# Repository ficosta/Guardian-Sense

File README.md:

# GuardianSense

**GuardianSense** is a versatile hardware project based on the ESP32-S3, designed to monitor environmental conditions and provide real-time data to **Zabbix**. This board is compact yet powerful, integrating multiple sensors for a wide range of applications, including data centers, smart homes, and industrial environments.

## Features

- **Core Module**: ESP32-S3-WROOM-1 for Wi-Fi and BLE connectivity.
- **Environmental Sensors**:
  - Temperature and Humidity (BME280)
  - Smoke Detection (MQ-2)
  - Light Intensity (BH1750)
  - Presence Detection (AM312 PIR Sensor)
  - Vibration Monitoring (LDT0-028K)
  - Noise Level Monitoring (MAX9814)
- **Indicators**:
  - Status LED (Single color)
  - RGB LED (SK6812-MINI-E)
- **Connectivity**:
  - USB-C for power and data
  - Multiple GPIOs for additional customizations
- **Power Management**:
  - Integrated voltage regulator for 3.3V operation.

## Firmware

The firmware for GuardianSense is tailored to interact with **Zabbix**, providing seamless integration with this monitoring platform. It supports real-time data transmission for:

- Temperature and humidity
- Smoke and gas levels
- Light intensity
- Vibration and noise detection

## Usage

1. Clone this repository:
   ```bash
   git clone https://github.com/ficosta/Guardian-Sense.git
   ```

2. Install KiCad for hardware design modifications (optional).

3. Flash the firmware to the ESP32-S3 module.

4. Configure Zabbix to accept incoming data from the board.

## KiCad Design Files

All hardware design files for GuardianSense are included in the `/hardware` directory. Make sure to follow the project's **.gitignore** for KiCad files when contributing.

## Contributing

Contributions are welcome! Please ensure that any hardware or firmware changes align with the project's goals.

## License

See the `LICENSE` file for more details.

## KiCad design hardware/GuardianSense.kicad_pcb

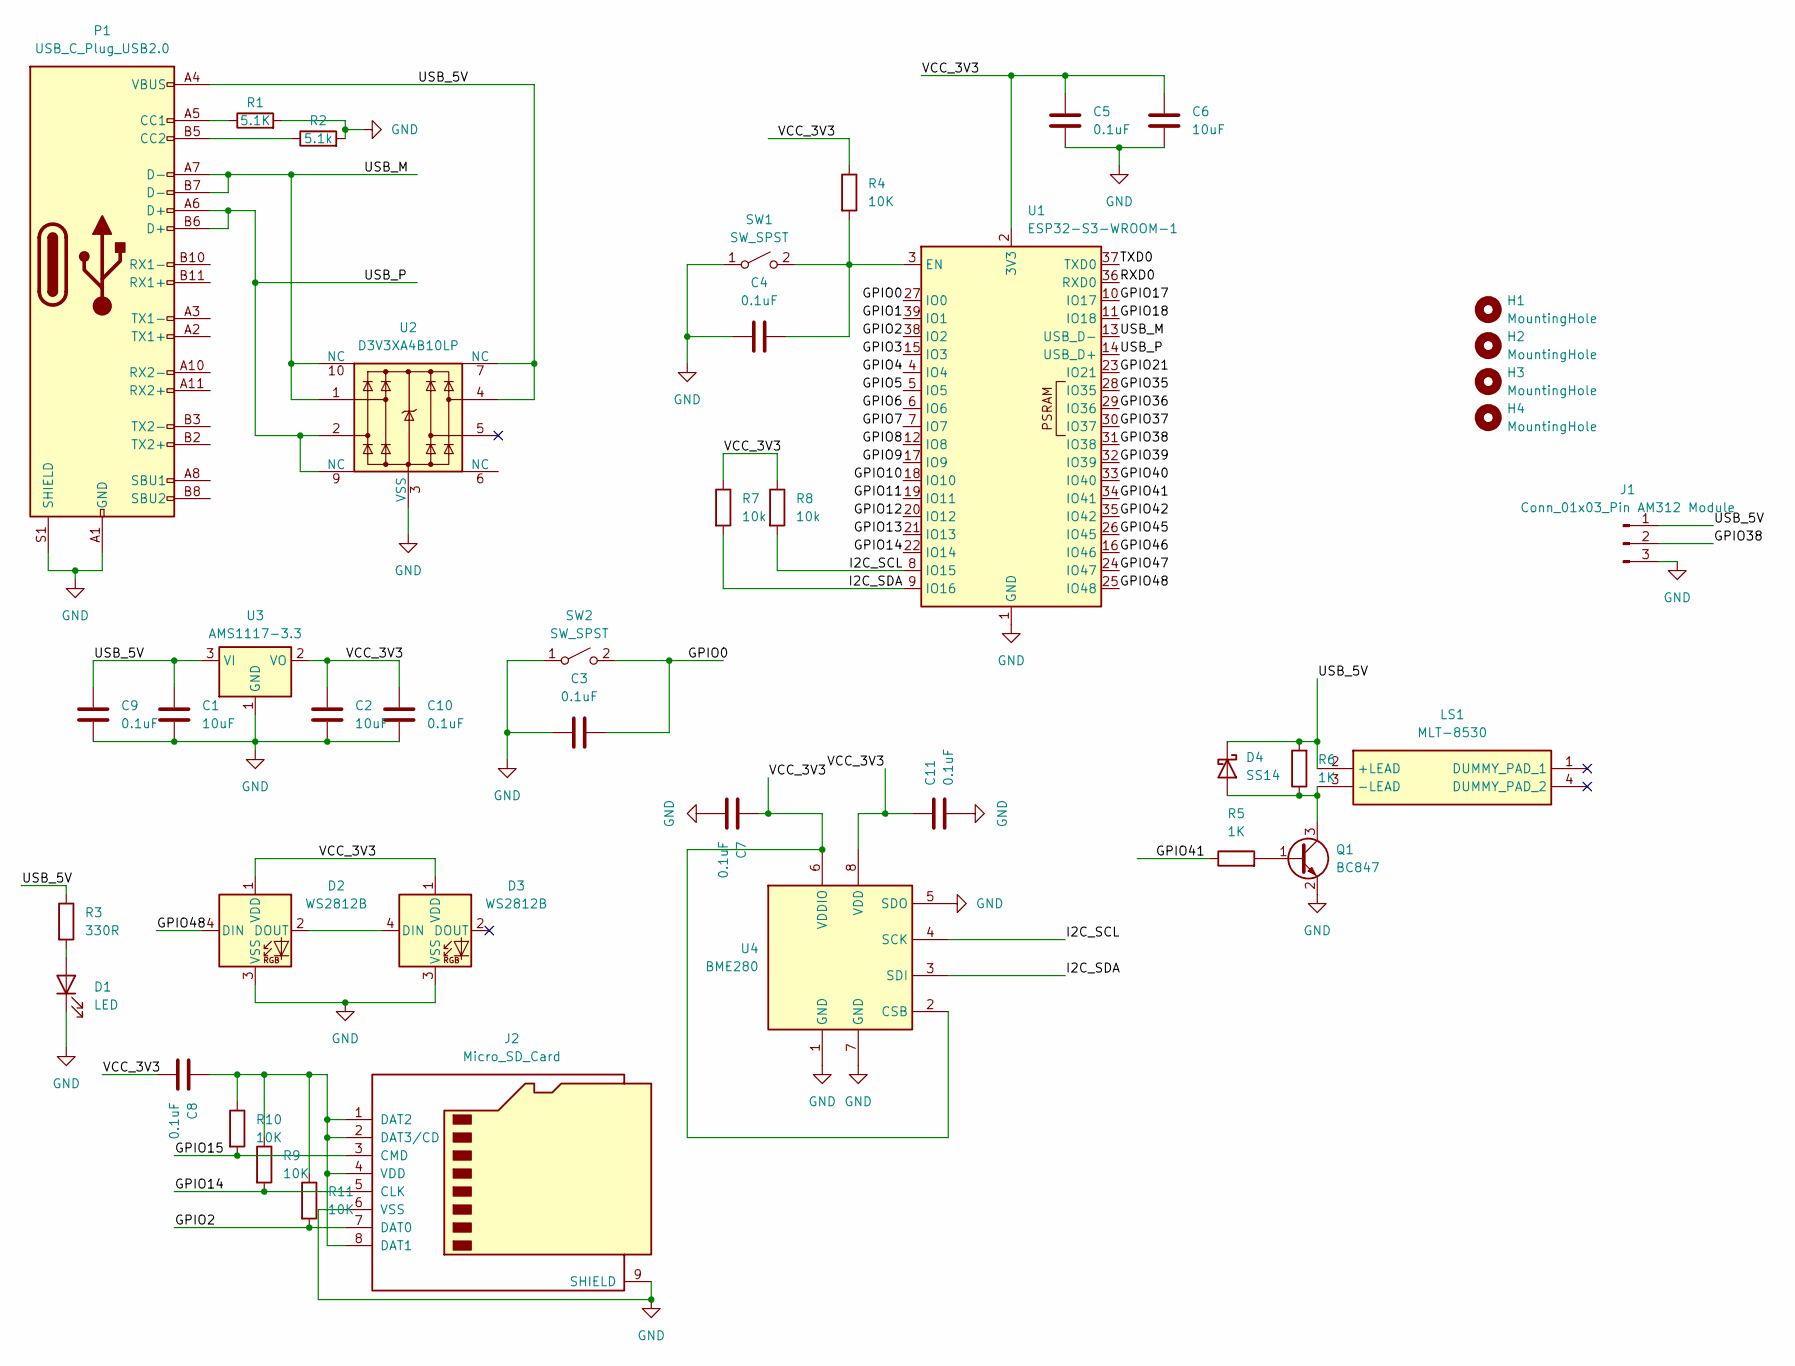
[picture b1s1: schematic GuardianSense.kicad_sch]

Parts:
C1, C2: 10uF; CP_Elec_4x5.4
C3, C4, C5, C7, C8, C9, C10, C11: 0.1uF; C_0805_2012Metric
C6: 10uF; C_0805_2012Metric
D1: LED; LED_0805_2012Metric
D2, D3: WS2812B; LED_WS2812B_PLCC4_5.0x5.0mm_P3.2mm
D4: SS14; D_SMA
H1, H2, H3, H4: MountingHole; MountingHole_3.2mm_M3_DIN965_Pad
J1: Conn_01x03_Pin AM312 Module; PinHeader_1x03_P2.54mm_Vertical
J2: Micro_SD_Card; AMPHENOL_GTFP08431BEU
LS1: MLT-8530; MLT8530; Manufacturer_Part_Number MLT-8530
P1: USB_C_Plug_USB2.0; USB-SMD_USB-TYPE-C-020
Q1: BC847; SOT-23
R1: 5.1K; R_0805_2012Metric
R2: 5.1k; R_0805_2012Metric
R3: 330R; R_0805_2012Metric
R4, R9, R10, R11: 10K; R_0805_2012Metric
R5, R6: 1K; R_0805_2012Metric
R7, R8: 10k; R_0805_2012Metric
SW1, SW2: SW_SPST; SW_Push_1P1T_XKB_TS-1187A
U1: ESP32-S3-WROOM-1
U2: D3V3XA4B10LP; Diodes_UDFN-10_1.0x2.5mm_P0.5mm
U3: AMS1117-3.3; SOT-223-3_TabPin2
U4: BME280; Bosch_LGA-8_2.5x2.5mm_P0.65mm_ClockwisePinNumbering

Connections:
/GPIO0: C3.2, SW2.2 (B), U1.27 (IO0)
/GPIO1: U1.39 (IO1)
/GPIO2: J2.7 (DAT0), R11.2, U1.38 (IO2)
/GPIO3: U1.15 (IO3)
/GPIO4: U1.4 (IO4)
/GPIO5: U1.5 (IO5)
/GPIO6: U1.6 (IO6)
/GPIO7: U1.7 (IO7)
/GPIO8: U1.12 (IO8)
/GPIO9: U1.17 (IO9)
/GPIO10: U1.18 (IO10)
/GPIO11: U1.19 (IO11)
/GPIO12: U1.20 (IO12)
/GPIO13: U1.21 (IO13)
/GPIO14: J2.5 (CLK), R9.2, U1.22 (IO14)
/GPIO15: J2.3 (CMD), R10.2
/GPIO17: U1.10 (IO17)
/GPIO18: U1.11 (IO18)
/GPIO21: U1.23 (IO21)
/GPIO35: U1.28 (IO35)
/GPIO36: U1.29 (IO36)
/GPIO37: U1.30 (IO37)
/GPIO38: J1.2, U1.31 (IO38)
/GPIO39: U1.32 (IO39)
/GPIO40: U1.33 (IO40)
/GPIO41: R5.1, U1.34 (IO41)
/GPIO42: U1.35 (IO42)
/GPIO45: U1.26 (IO45)
/GPIO46: U1.16 (IO46)
/GPIO47: U1.24 (IO47)
/GPIO48: D2.4 (DIN), U1.25 (IO48)
/I2C_SCL: R8.2, U1.8 (IO15), U4.4 (SCK)
/I2C_SDA: R7.2, U1.9 (IO16), U4.3 (SDI)
/RXD0: U1.36 (RXD0)
/TXD0: U1.37 (TXD0)
/USB_5V: C1.1, C9.1, D4.1 (K), J1.1, LS1.2 (+LEAD), P1.A4 (VBUS), P1.A9 (VBUS), P1.B4 (VBUS), P1.B9 (VBUS), R3.1, R6.2, U2.4, U2.7 (NC), U3.3 (VI)
/USB_M: P1.A7 (D-), P1.B7 (D-), U1.13 (USB_D-), U2.1, U2.10 (NC)
/USB_P: P1.A6 (D+), P1.B6 (D+), U1.14 (USB_D+), U2.2, U2.9 (NC)
/VCC_3V3: C2.1, C5.2, C6.2, C7.1, C8.2, C10.1, C11.1, D2.1 (VDD), D3.1 (VDD), R4.1, R7.1, R8.1, U1.2 (3V3), U3.2 (VO), U4.2 (CSB), U4.6 (VDDIO), U4.8 (VDD)
GND: C1.2, C2.2, C3.1, C4.1, C5.1, C6.1, C7.2, C9.2, C10.2, C11.2, D1.1 (K), D2.3 (VSS), D3.3 (VSS), J1.3, J2.6 (VSS), J2.9 (SHIELD), P1.A1 (GND), P1.A12 (GND), P1.B1 (GND), P1.B12 (GND), P1.S1 (SHIELD), Q1.2 (E), R1.2, R2.2, SW1.1 (A), SW2.1 (A), U1.1 (GND), U1.40 (GND), U1.41 (GND), U2.3 (VSS), U2.8 (VSS), U3.1 (GND), U4.1 (GND), U4.5 (SDO), U4.7 (GND)
unnamed: D1.2 (A), R3.2
unnamed: D2.2 (DOUT), D3.4 (DIN)
unnamed: D4.2 (A), LS1.3 (-LEAD), Q1.3 (C), R6.1
unnamed: C8.1, J2.1 (DAT2), J2.2 (DAT3/CD), J2.4 (VDD), J2.8 (DAT1), R9.1, R10.1, R11.1
unnamed: P1.A5 (CC1), R1.1
unnamed: P1.B5 (CC2), R2.1
unnamed: Q1.1 (B), R5.2
unnamed: C4.2, R4.2, SW1.2 (B), U1.3 (EN)

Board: 2 copper layers, 38 parts (0 on the bottom side), 19 nets, no tracks yet.

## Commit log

2025-01-05 Sunday Fun!
2025-01-06 Updates Monday
